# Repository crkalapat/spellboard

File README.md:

# Spellboard

_A large key cap custom keyboard, designed for spelling to communicate._

## Features

- Letter layout matching [Spellers](https://www.spellers.com/product-page/large-a-z-stencil) stencil letter board
- All 26 letters in alphabet
- Capitalize, Backspace, Enter, Space keys
- USB C connectivity
- Custom large keycaps for less reliance on fine motor skills

## Demo

https://github.com/user-attachments/assets/92936077-01a1-442b-ba66-4622e2b436ea

## BOM

- 30x 2-Pin key switches
- 30x SOD-123 diodes
- Seeed Studio XIAO RP2040
- 1x PCB
- 1x 3D Printed Enclosure Left
- 1x 3D Printed Enclosure Right
- 1x Backplate
- 8x M3x8mm screws
- 8x M3 nuts

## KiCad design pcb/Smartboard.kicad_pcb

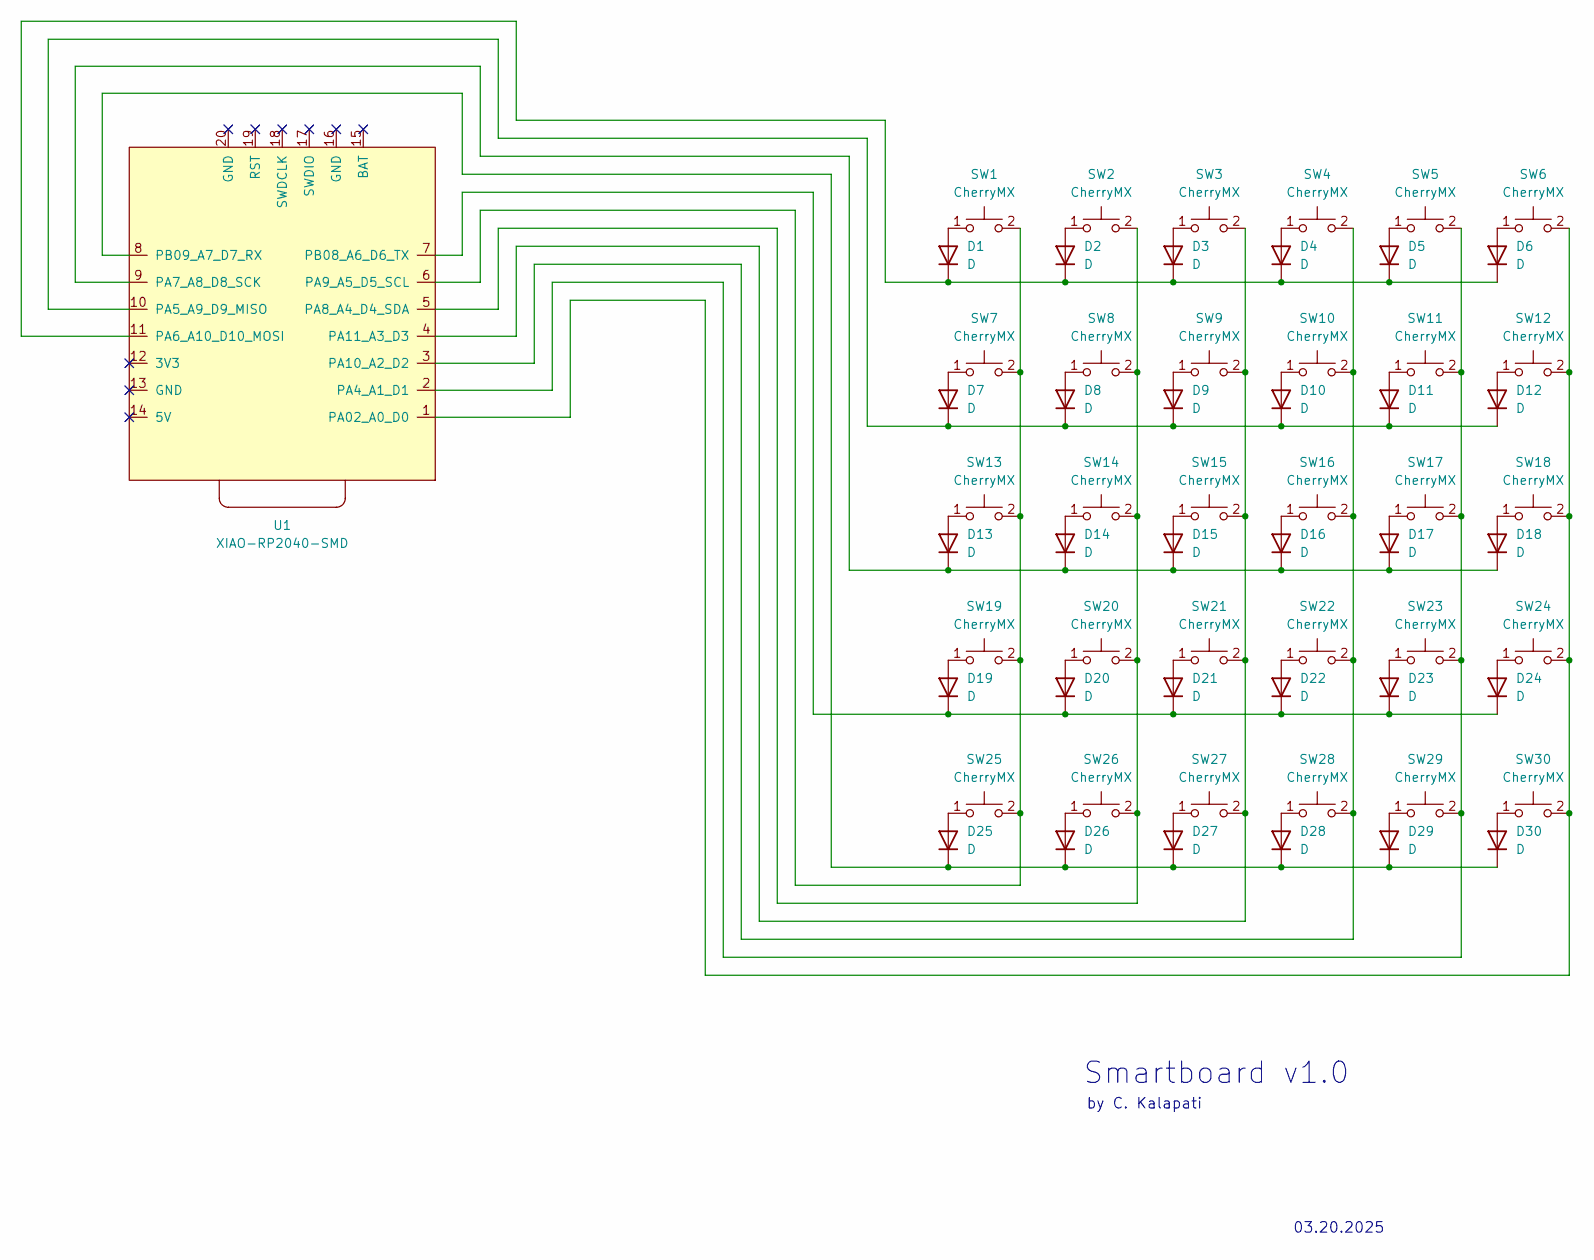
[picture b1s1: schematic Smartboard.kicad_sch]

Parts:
D1, D2, D3, D4, D5, D6, D7, D8, D9, D10, D11, D12, D13, D14, D15, D16, D17, D18, D19, D20, D21, D22, D23, D24, D25, D26, D27, D28, D29, D30: D; D_0805_2012Metric
SW1, SW2, SW3, SW4, SW5, SW6, SW7, SW8, SW9, SW10, SW11, SW12, SW13, SW14, SW15, SW16, SW17, SW18, SW19, SW20, SW21, SW22, SW23, SW24, SW25, SW26, SW27, SW28, SW29, SW30: CherryMX; CherryMX_1.00u
U1: XIAO-RP2040-SMD; XIAO-nRF52840-SMD

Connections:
unnamed: D1.2 (A), SW1.1
unnamed: D1.1 (K), D2.1 (K), D3.1 (K), D4.1 (K), D5.1 (K), D6.1 (K), U1.11 (PA11_A3_D3)
unnamed: D2.2 (A), SW2.1
unnamed: D3.2 (A), SW3.1
unnamed: D4.2 (A), SW4.1
unnamed: D5.2 (A), SW5.1
unnamed: D6.2 (A), SW6.1
unnamed: D7.2 (A), SW7.1
unnamed: D8.2 (A), SW8.1
unnamed: D9.2 (A), SW9.1
unnamed: D10.2 (A), SW10.1
unnamed: D7.1 (K), D8.1 (K), D9.1 (K), D10.1 (K), D11.1 (K), D12.1 (K), U1.10 (PA8_A4_D4_SDA)
unnamed: D11.2 (A), SW11.1
unnamed: D12.2 (A), SW12.1
unnamed: D13.2 (A), SW13.1
unnamed: D13.1 (K), D14.1 (K), D15.1 (K), D16.1 (K), D17.1 (K), D18.1 (K), U1.9 (PA9_A5_D5_SCL)
unnamed: D14.2 (A), SW14.1
unnamed: D15.2 (A), SW15.1
unnamed: D16.2 (A), SW16.1
unnamed: D17.2 (A), SW17.1
unnamed: D18.2 (A), SW18.1
unnamed: D19.2 (A), SW19.1
unnamed: D19.1 (K), D20.1 (K), D21.1 (K), D22.1 (K), D23.1 (K), D24.1 (K), U1.7 (PB09_A7_D7_RX)
unnamed: D20.2 (A), SW20.1
unnamed: D21.2 (A), SW21.1
unnamed: D22.2 (A), SW22.1
unnamed: D23.2 (A), SW23.1
unnamed: D24.2 (A), SW24.1
unnamed: D25.2 (A), SW25.1
unnamed: D25.1 (K), D26.1 (K), D27.1 (K), D28.1 (K), D29.1 (K), D30.1 (K), U1.8 (PB08_A6_D6_TX)
unnamed: D26.2 (A), SW26.1
unnamed: D27.2 (A), SW27.1
unnamed: D28.2 (A), SW28.1
unnamed: D29.2 (A), SW29.1
unnamed: D30.2 (A), SW30.1
unnamed: SW6.2, SW12.2, SW18.2, SW24.2, SW30.2, U1.1 (5V)
unnamed: SW5.2, SW11.2, SW17.2, SW23.2, SW29.2, U1.2 (GND)
unnamed: SW2.2, SW8.2, SW14.2, SW20.2, SW26.2, U1.5 (PA5_A9_D9_MISO)
unnamed: SW1.2, SW7.2, SW13.2, SW19.2, SW25.2, U1.6 (PA7_A8_D8_SCK)
unnamed: SW4.2, SW10.2, SW16.2, SW22.2, SW28.2, U1.3 (3V3)
unnamed: SW3.2, SW9.2, SW15.2, SW21.2, SW27.2, U1.4 (PA6_A10_D10_MOSI)

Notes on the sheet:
03.20.2025
Smartboard v1.0
by C. Kalapati

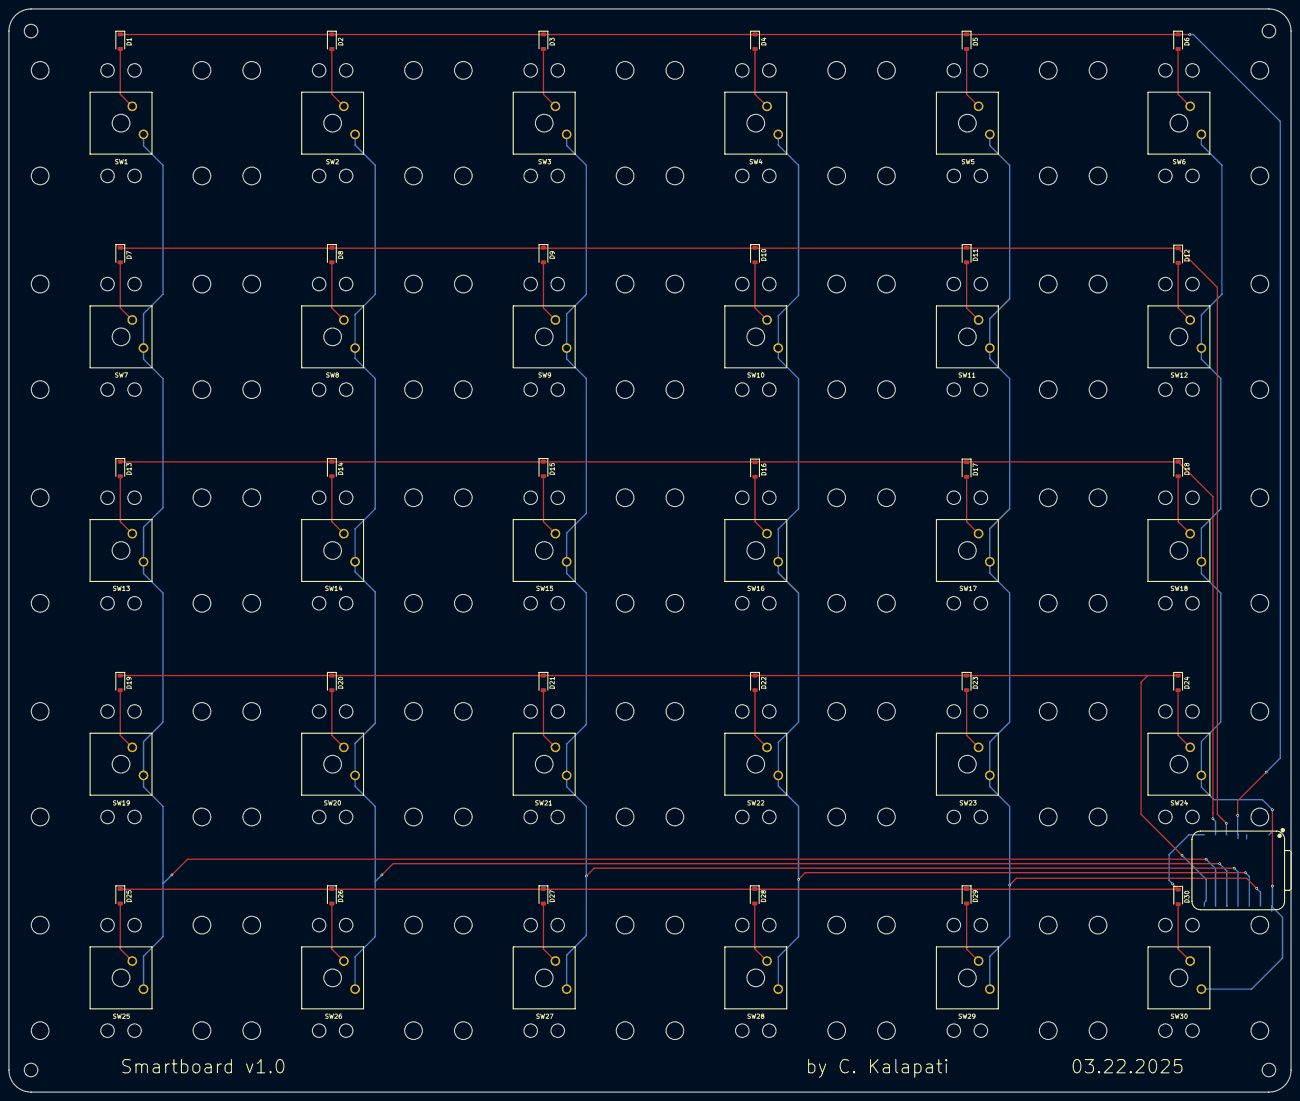
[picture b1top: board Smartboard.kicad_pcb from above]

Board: 2 copper layers, 290.0 x 245.0 mm, 61 parts (0 on the bottom side), 41 nets.

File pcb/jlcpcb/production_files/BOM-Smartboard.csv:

Comment,Designator,Footprint,LCSC,Quantity
D,"D1,D10,D11,D12,D13,D14,D15,D16,D17,D18,D19,D2,D20,D21,D22,D23,D24,D25,D26,D27,D28,D29,D3,D30,D4,D5,D6,D7,D8,D9",D_SOD-123,C2099,30
CherryMX,SW8,CherryMX_1.00u,,1
CherryMX,SW27,CherryMX_1.00u,,1
CherryMX,SW17,CherryMX_1.00u,,1
CherryMX,SW30,CherryMX_1.00u,,1
CherryMX,SW20,CherryMX_1.00u,,1
CherryMX,SW25,CherryMX_1.00u,,1
CherryMX,SW3,CherryMX_1.00u,,1
CherryMX,SW11,CherryMX_1.00u,,1
CherryMX,SW18,CherryMX_1.00u,,1
CherryMX,SW4,CherryMX_1.00u,,1
CherryMX,SW7,CherryMX_1.00u,,1
CherryMX,SW13,CherryMX_1.00u,,1
CherryMX,SW14,CherryMX_1.00u,,1
CherryMX,SW29,CherryMX_1.00u,,1
CherryMX,SW26,CherryMX_1.00u,,1
CherryMX,SW5,CherryMX_1.00u,,1
CherryMX,SW12,CherryMX_1.00u,,1
CherryMX,SW22,CherryMX_1.00u,,1
CherryMX,SW24,CherryMX_1.00u,,1
CherryMX,SW6,CherryMX_1.00u,,1
CherryMX,SW1,CherryMX_1.00u,,1
CherryMX,SW19,CherryMX_1.00u,,1
CherryMX,SW2,CherryMX_1.00u,,1
CherryMX,SW21,CherryMX_1.00u,,1
CherryMX,SW28,CherryMX_1.00u,,1
CherryMX,SW9,CherryMX_1.00u,,1
CherryMX,SW15,CherryMX_1.00u,,1
CherryMX,SW10,CherryMX_1.00u,,1
CherryMX,SW23,CherryMX_1.00u,,1
CherryMX,SW16,CherryMX_1.00u,,1
XIAO-SMD,U1,XIAO-nRF52840-SMD,,1

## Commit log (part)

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2025-10-15 Add project files
2025-10-15 Left align image in README
2025-10-15 Make project image wider in README
2025-10-15 Add BOM in README
2025-10-15 Add screws to BOM in README
2026-01-06 Add firmware files
2026-06-22 Add demo video and gitignore
2026-06-22 Speed up demo
2026-06-22 Trim and cut down demo
2026-06-22 Fix demo video in README
